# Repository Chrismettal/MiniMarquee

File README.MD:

# Update

v0.3 newly uses only a 10uF input cap instead of a 100uF one, since the inrush current when plugging in your PSU made some cheaper 100uF caps fail in rare occasions even with 50% volate derating. a 10uF 35 V cap is effectively using a 2/3 derating and is much less likely to fail, even when cheaper caps are used. Because of the violence of failing tantalum caps a v0.4 will be made that does not use tantalums at all in the future. For that reason v0.3 gerbers are not tested, but have just been generated after changing the silkscreen value of the input cap.

# Buying

I have opened up a Tindie store, carrying PCBs and DIY kits as well as 3D printed parts for this and other projects!

**If you like my work please consider [supporting my caffeine addiction](https://github.com/Chrismettal#donations)!**

- [Update](#update)
- [Buying](#buying)
  - [What is this](#what-is-this)
  - [Capabilities](#capabilities)
  - [DIY](#diy)
  - [Power](#power)
  - [Versions](#versions)
  - [Controls](#controls)
  - [Scenes](#scenes)
  - [Signs](#signs)

## What is this

Small marquees for standalone decoration with backlit signs, including output for up to 25 W of RGB LED strip.

Might be used for multiple consoles to have the specific sign and indirect strip lighting light up with the console.

## Capabilities

At the moment 15 light scenes can be hardcoded including static light ones and fading between 2 colors. More complex fades can be accomplished at will with any number of calculations with the iFade variables. The amount of light scenes and their values can be modified in the source. The same light scenes will be used for the backlight and the RGB strip output, but the two "zones" can be individually set to display a different scene to enable a contrast between the sign and indirect lighting. A single button steps through the light scenes for the specific zones. The current light scene is always saved in EEPROM to stay persistent between power cycles.

## DIY

**For detailed instructions, check out [the full build guide](/doc/Build_Guide.md), [how to edit light scenes](/doc/Edit_Light_Scenes.md) as well as [the troubleshooting guide](doc/Troubleshooting.md)**

All the files are open source. The gerber files as well as the KiCAD project files can be found to get the PCBs made.

The case as well as all the signs need to be 3D printed. For the signs at least a 2-color extruder is required. I print all the parts in PETG because of the selection of transparent materials. The lowermost part I print in white for case internal reflections but if you only have a dual extruder setup you can print the lower and upper parts both in black and the actual logo in your color of choice.

Soldering requires some SMD capabilities. The QFP32 chip is the hardest but with a bit of flux is actually quite doable.

You don't need to change anything in the source if you are fine with the preconfigured lightscenes.
All light scenes are hardcoded in the `LightSceneEvaluation()` function. See the commented examples to make your own scenes. Also check out the [light scene documentation](/doc/Edit_Light_Scenes.md).
I used [PlatformIO](https://platformio.org/) on Visual Studio Code for programming. You could upload the code with the Arduino IDE but i recommend giving PlatformIO a try as you won't have to deal with the libraries etc. yourself.
An ICSP programmer is required to upload code to the board. I used a cheap UBSTiny device but you could use an *Arduino as ISP* for example.

## Power

The device can be powered directly by a 12 V DC power supply. In my usecase the "master" device that controls the power to the individual consoles also switches on/off the power to the marquees, but you could power the marquees directly from the console using DC-DC converters to make the marquee always switch on with the console. 

## Versions

The current PCB version is v0.2.
The source code is made to be adaptable to both v0.2 and v0.1 PCBs to use with the old revision of the PCB. By default v0.2 is defined in the software. You will have to uncomment the "#define PCB_v0_1" to use the code with the old v0.1 PCB version, should you happen to get your hands on one.

## Controls

- Button short click    --> Next lightscene in current light zone
- Button double click   --> Previous lightscene in current light zone
- Button long click     --> Switch between which light zone to change

The device can just be switched on and off by cutting the power to it. It will remember its lightscenes for the next boot.

## Scenes

For now 15 lightscenes are precoded:

- Red
- Green
- Blue
- Sky Blue
- Warm white
- Cold white
- Yelow
- Orange
- Purple
- Olive
- Slow fade between Red and Green
- Slow fade between Green and Blue
- Slow fade between Blue and Red
- Slow fade between Yellow and Blue
- Breathing white

For not the Scenes are the same for internal and external lightzone but they don't have to be, should you want to change that.

**For detailed instructions, [how to edit light scenes](/doc/Edit_Light_Scenes.md)**

## Signs

This is an example of some of the designed signs. I am still in the process of printing out every one of them so i don't yet have pictures of all signs ready.

I also uploaded the "RawSign" files in the 3d printable folder so you can design your own signs. Be sure to reupload them either as a remix on [The Thingiverse page](https://www.thingiverse.com/thing:3683055) or somewhere else where i can feed them back into here.

Here is a list of the already made signs:

- [ ]  Nintendo
- [x]  NES
- [x]  SNES
- [x]  N64
- [x]  GC
- [x]  Wii
- [x]  WiiU
- [x]  Switch
- [x]  PS1
- [x]  PS2
- [x]  PS3
- [x]  PS4
- [x]  Xbox Classic
- [x]  Xbox 360
- [x]  Xbox One
- [ ]  Sega
- [x]  Master System
- [x]  Genesis
- [ ]  Megadrive
- [x]  Dreamcast
- [x]  Atari 2600
- [x]  NeoGeo
- [x]  Commodore
- [ ]  PC Engine
- [ ]  Turbografx 16
- [x]  Diffuse plate for stickers

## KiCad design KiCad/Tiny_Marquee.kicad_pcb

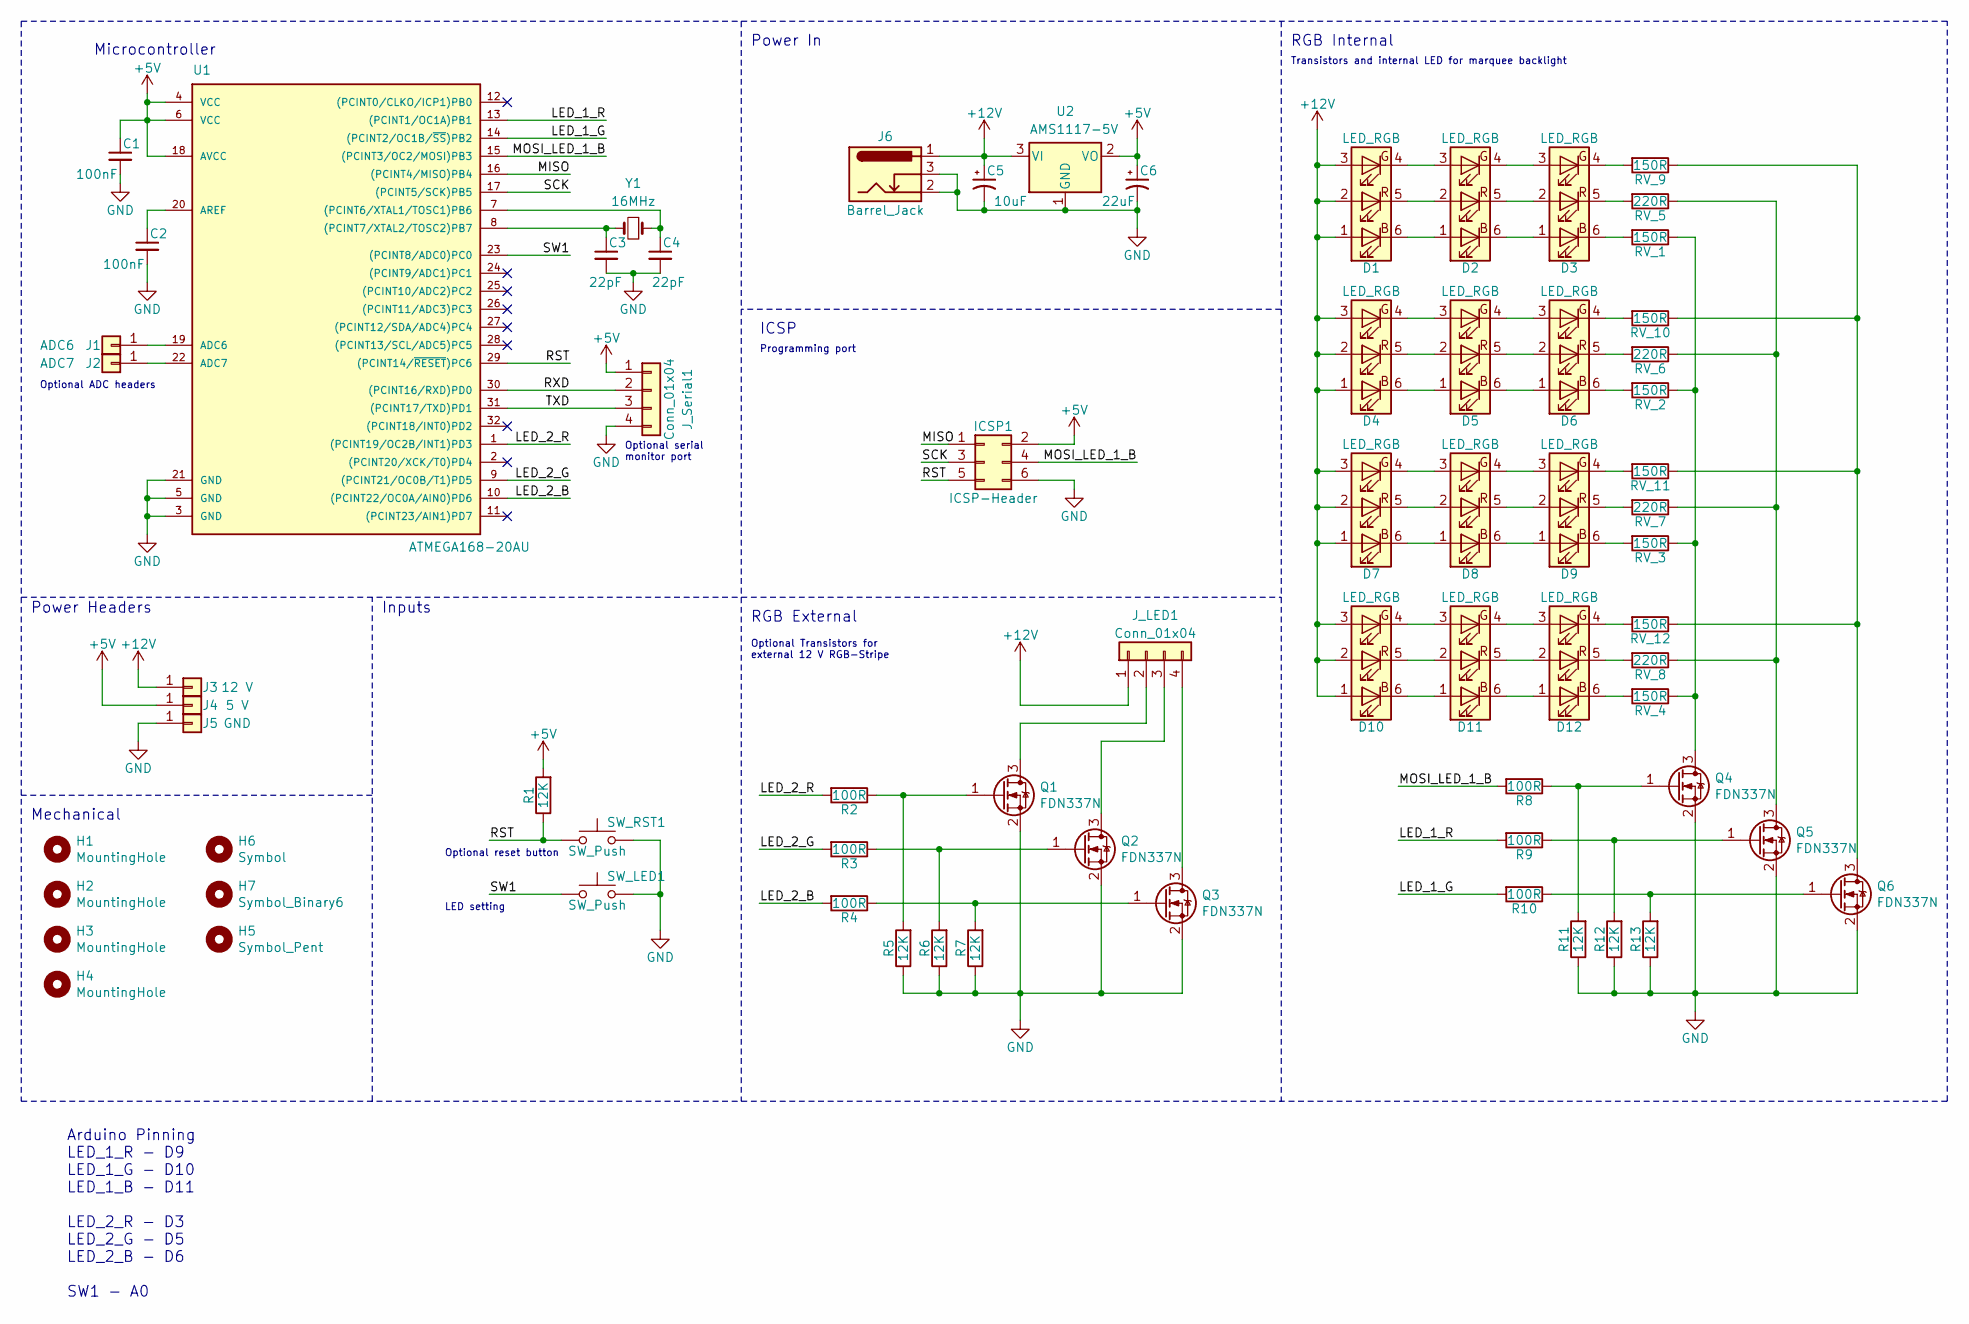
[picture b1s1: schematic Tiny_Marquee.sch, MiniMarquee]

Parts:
C1, C2: 100nF; C_0805_2012Metric_Pad1.15x1.40mm_HandSolder
C3, C4: 22pF; C_0805_2012Metric_Pad1.15x1.40mm_HandSolder
C5: 10uF; CP_EIA-7343-15_Kemet-W_Pad2.25x2.55mm_HandSolder
C6: 22uF; CP_EIA-3528-15_AVX-H_Pad1.50x2.35mm_HandSolder
D1, D2, D3, D4, D5, D6, D7, D8, D9, D10, D11, D12: LED_RGB; LED_RGB_5050-6
H1, H2, H3, H4: MountingHole; EigenesMountingHole_2.7mm_M2.5
H5: Symbol_Pent; PentThin
H6: Symbol; Symbol_KiCAD-Logo_CopperAndSilkScreenTop
H7: Symbol_Binary6; Binary_6_v0.1
ICSP1: ICSP-Header; AVR_ISP
J1: ADC6; PinheaderOwnWithoutSilk
J2: ADC7; PinheaderOwnWithoutSilk
J3: 12 V; PinheaderOwnWithoutSilk
J4: 5 V; PinheaderOwnWithoutSilk
J5: GND; PinheaderOwnWithoutSilk
J6: Barrel_Jack; DC_Barrel_Jack_Standing
J_LED1: Conn_01x04; PinSocket_1x04_P2.54mm_Vertical
J_Serial1: Conn_01x04; PinSocket_1x04_P2.54mm_Vertical
Q1, Q2, Q3, Q4, Q5, Q6: FDN337N; SOT-23
R1, R5, R6, R7, R11, R12, R13: 12K; R_0805_2012Metric_Pad1.15x1.40mm_HandSolder
R2, R3, R4, R8, R9, R10: 100R; R_0805_2012Metric_Pad1.15x1.40mm_HandSolder
RV_1, RV_2, RV_3, RV_4, RV_9, RV_10, RV_11, RV_12: 150R; R_0805_2012Metric_Pad1.15x1.40mm_HandSolder
RV_5, RV_6, RV_7, RV_8: 220R; R_0805_2012Metric_Pad1.15x1.40mm_HandSolder
SW_LED1: SW_Push; SW_PUSH_6mm_H9.5mm
SW_RST1: SW_Push; SW_PUSH_6mm
U1: ATMEGA168-20AU; TQFP-32_7x7mm_P0.8mm
U2: AMS1117-5V; SOT-223-3_TabPin2
Y1: 16MHz; Crystal_SMD_HC49-SD

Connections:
+5V: C1.1, C6.1, ICSP1.2, J4.1, J_Serial1.1, R1.2, U1.4 (VCC), U1.6 (VCC), U1.18 (AVCC), U2.2 (VO)
+12V: C5.1, D1.1 (RA), D1.2 (GA), D1.3 (BA), D4.1 (RA), D4.2 (GA), D4.3 (BA), D7.1 (RA), D7.2 (GA), D7.3 (BA), D10.1 (RA), D10.2 (GA), D10.3 (BA), J3.1, J6.1, J_LED1.1, U2.3 (VI)
/LED_1_G: R10.2, U1.14 ((PCINT2/OC1B/~SS~)PB2)
/LED_1_R: R9.2, U1.13 ((PCINT1/OC1A)PB1)
/LED_2_B: R4.2, U1.10 ((PCINT22/OC0A/AIN0)PD6)
/LED_2_G: R3.2, U1.9 ((PCINT21/OC0B/T1)PD5)
/LED_2_R: R2.2, U1.1 ((PCINT19/OC2B/INT1)PD3)
/MISO: ICSP1.1, U1.16 ((PCINT4/MISO)PB4)
/MOSI_LED_1_B: ICSP1.4, R8.2, U1.15 ((PCINT3/OC2/MOSI)PB3)
/RST: ICSP1.5, R1.1, SW_RST1.1, U1.29 ((PCINT14/~RESET~)PC6)
/RXD: J_Serial1.2, U1.30 ((PCINT16/RXD)PD0)
/SCK: ICSP1.3, U1.17 ((PCINT5/SCK)PB5)
/SW1: SW_LED1.1, U1.23 ((PCINT8/ADC0)PC0)
/TXD: J_Serial1.3, U1.31 ((PCINT17/TXD)PD1)
GND: C1.2, C2.2, C3.2, C4.2, C5.2, C6.2, ICSP1.6, J5.1, J6.2, J6.3, J_Serial1.4, Q1.2 (S), Q2.2 (S), Q3.2 (S), Q4.2 (S), Q5.2 (S), Q6.2 (S), R5.1, R6.1, R7.1, R11.1, R12.1, R13.1, SW_LED1.2, SW_RST1.2, U1.3 (GND), U1.5 (GND), U1.21 (GND), U2.1 (GND)
unnamed: C2.1, U1.20 (AREF)
unnamed: C3.1, U1.8 ((PCINT7/XTAL2/TOSC2)PB7), Y1.2
unnamed: C4.1, U1.7 ((PCINT6/XTAL1/TOSC1)PB6), Y1.1
unnamed: D1.4 (BK), D2.3 (BA)
unnamed: D1.5 (GK), D2.2 (GA)
unnamed: D1.6 (RK), D2.1 (RA)
unnamed: D2.4 (BK), D3.3 (BA)
unnamed: D2.5 (GK), D3.2 (GA)
unnamed: D2.6 (RK), D3.1 (RA)
unnamed: D3.4 (BK), RV_9.2
unnamed: D3.5 (GK), RV_5.2
unnamed: D3.6 (RK), RV_1.2
unnamed: D4.4 (BK), D5.3 (BA)
unnamed: D4.5 (GK), D5.2 (GA)
unnamed: D4.6 (RK), D5.1 (RA)
unnamed: D5.4 (BK), D6.3 (BA)
unnamed: D5.5 (GK), D6.2 (GA)
unnamed: D5.6 (RK), D6.1 (RA)
unnamed: D6.4 (BK), RV_10.2
unnamed: D6.5 (GK), RV_6.2
unnamed: D6.6 (RK), RV_2.2
unnamed: D7.4 (BK), D8.3 (BA)
unnamed: D7.5 (GK), D8.2 (GA)
unnamed: D7.6 (RK), D8.1 (RA)
unnamed: D8.4 (BK), D9.3 (BA)
unnamed: D8.5 (GK), D9.2 (GA)
unnamed: D8.6 (RK), D9.1 (RA)
unnamed: D9.4 (BK), RV_11.2
unnamed: D9.5 (GK), RV_7.2
unnamed: D9.6 (RK), RV_3.2
unnamed: D10.4 (BK), D11.3 (BA)
unnamed: D10.5 (GK), D11.2 (GA)
unnamed: D10.6 (RK), D11.1 (RA)
unnamed: D11.4 (BK), D12.3 (BA)
unnamed: D11.5 (GK), D12.2 (GA)
unnamed: D11.6 (RK), D12.1 (RA)
unnamed: D12.4 (BK), RV_12.2
unnamed: D12.5 (GK), RV_8.2
unnamed: D12.6 (RK), RV_4.2
unnamed: J1.1, U1.19 (ADC6)
unnamed: J2.1, U1.22 (ADC7)
unnamed: J_LED1.2, Q1.3 (D)
unnamed: J_LED1.3, Q2.3 (D)
unnamed: J_LED1.4, Q3.3 (D)
unnamed: Q1.1 (G), R2.1, R5.2
unnamed: Q2.1 (G), R3.1, R6.2
unnamed: Q3.1 (G), R4.1, R7.2
unnamed: Q4.1 (G), R8.1, R11.2
unnamed: Q4.3 (D), RV_1.1, RV_2.1, RV_3.1, RV_4.1
unnamed: Q5.1 (G), R9.1, R12.2
unnamed: Q5.3 (D), RV_5.1, RV_6.1, RV_7.1, RV_8.1
unnamed: Q6.1 (G), R10.1, R13.2
unnamed: Q6.3 (D), RV_9.1, RV_10.1, RV_11.1, RV_12.1

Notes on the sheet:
ICSP
Inputs
Microcontroller
RGB External
RGB Internal
LED setting
Optional reset button
Power In
Optional serial monitor port
Optional Transistors for external 12 V RGB-Stripe
Transistors and internal LED for marquee backlight
Programming port
Power Headers
Optional ADC headers
Mechanical
Arduino Pinning LED_1_R - D9 LED_1_G - D10 LED_1_B - D11 LED_2_R - D3 LED_2_G - D5 LED_2_B - D6 SW1 - A0

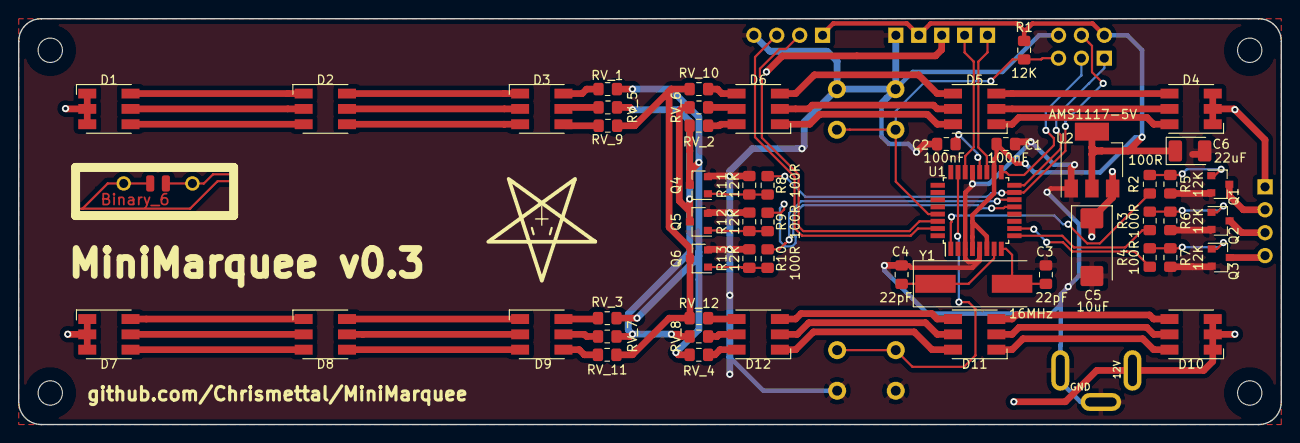
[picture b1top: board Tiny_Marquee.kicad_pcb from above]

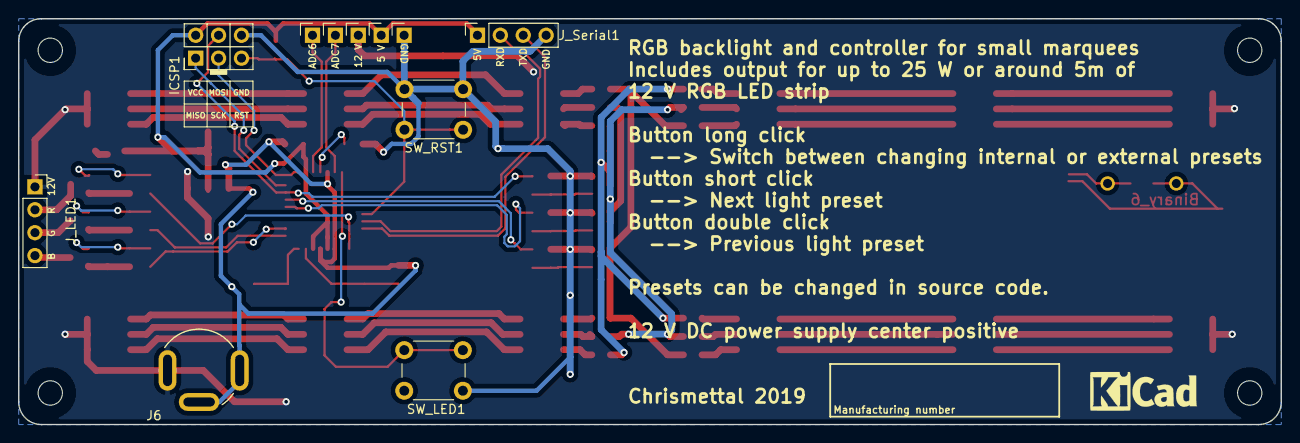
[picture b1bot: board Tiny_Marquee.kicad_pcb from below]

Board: 2 copper layers, 140.0 x 45.0 mm, 70 parts (12 on the bottom side), 68 nets.

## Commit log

2019-05-31 Deleted unneccessary file
2019-05-31 Added readme descriptions
2019-05-31 Updated source for use with PCB v0.1 and v0.2
2019-05-31 Uploaded pcb pictures
2019-05-31 Added pictures
2019-05-31 Inserted and renamed pictures
2019-05-31 Edited Readme
2019-05-31 Fixed sourcecode for both hw versions
2019-06-03 Update nothing
2019-06-03 Updated comment
2019-06-08 Fixed loading lightscenes on reboot
2019-06-09 Upload more material
2019-06-09 Added more shields
2019-06-09 Added even mode shields
2019-06-10 Made more signs
2019-06-10 namechange
2019-06-10 Switched folder layout
2019-06-10 Updated for release
2019-06-10 Added raw sign files
2019-06-20 Added more frontpanels
2019-06-21 New revision of case with diffusor and new light scenes
2019-06-21 Fixed light scene bug
2019-06-22 More planned signs
2019-06-28 Included libraries in project file and updated code
2019-06-29 Uploaded sign footage
2020-10-13 Add FUNDING.yml
2021-01-16 Update to v0.3, switching C5 to 10uF, 35 V.
2021-01-16 Cut away version number from logo
2021-05-27 Update readme with shopping information
2021-07-10 MOVING TO GITLAB
2021-08-21 Add license
2021-08-21 Add missing Wiki as markdown files
2021-08-21 Add troubleshooting info
2021-08-21 Fix some parts of README.MD
2021-08-21 Fix doc typo
2023-05-01 Remove Kofi
